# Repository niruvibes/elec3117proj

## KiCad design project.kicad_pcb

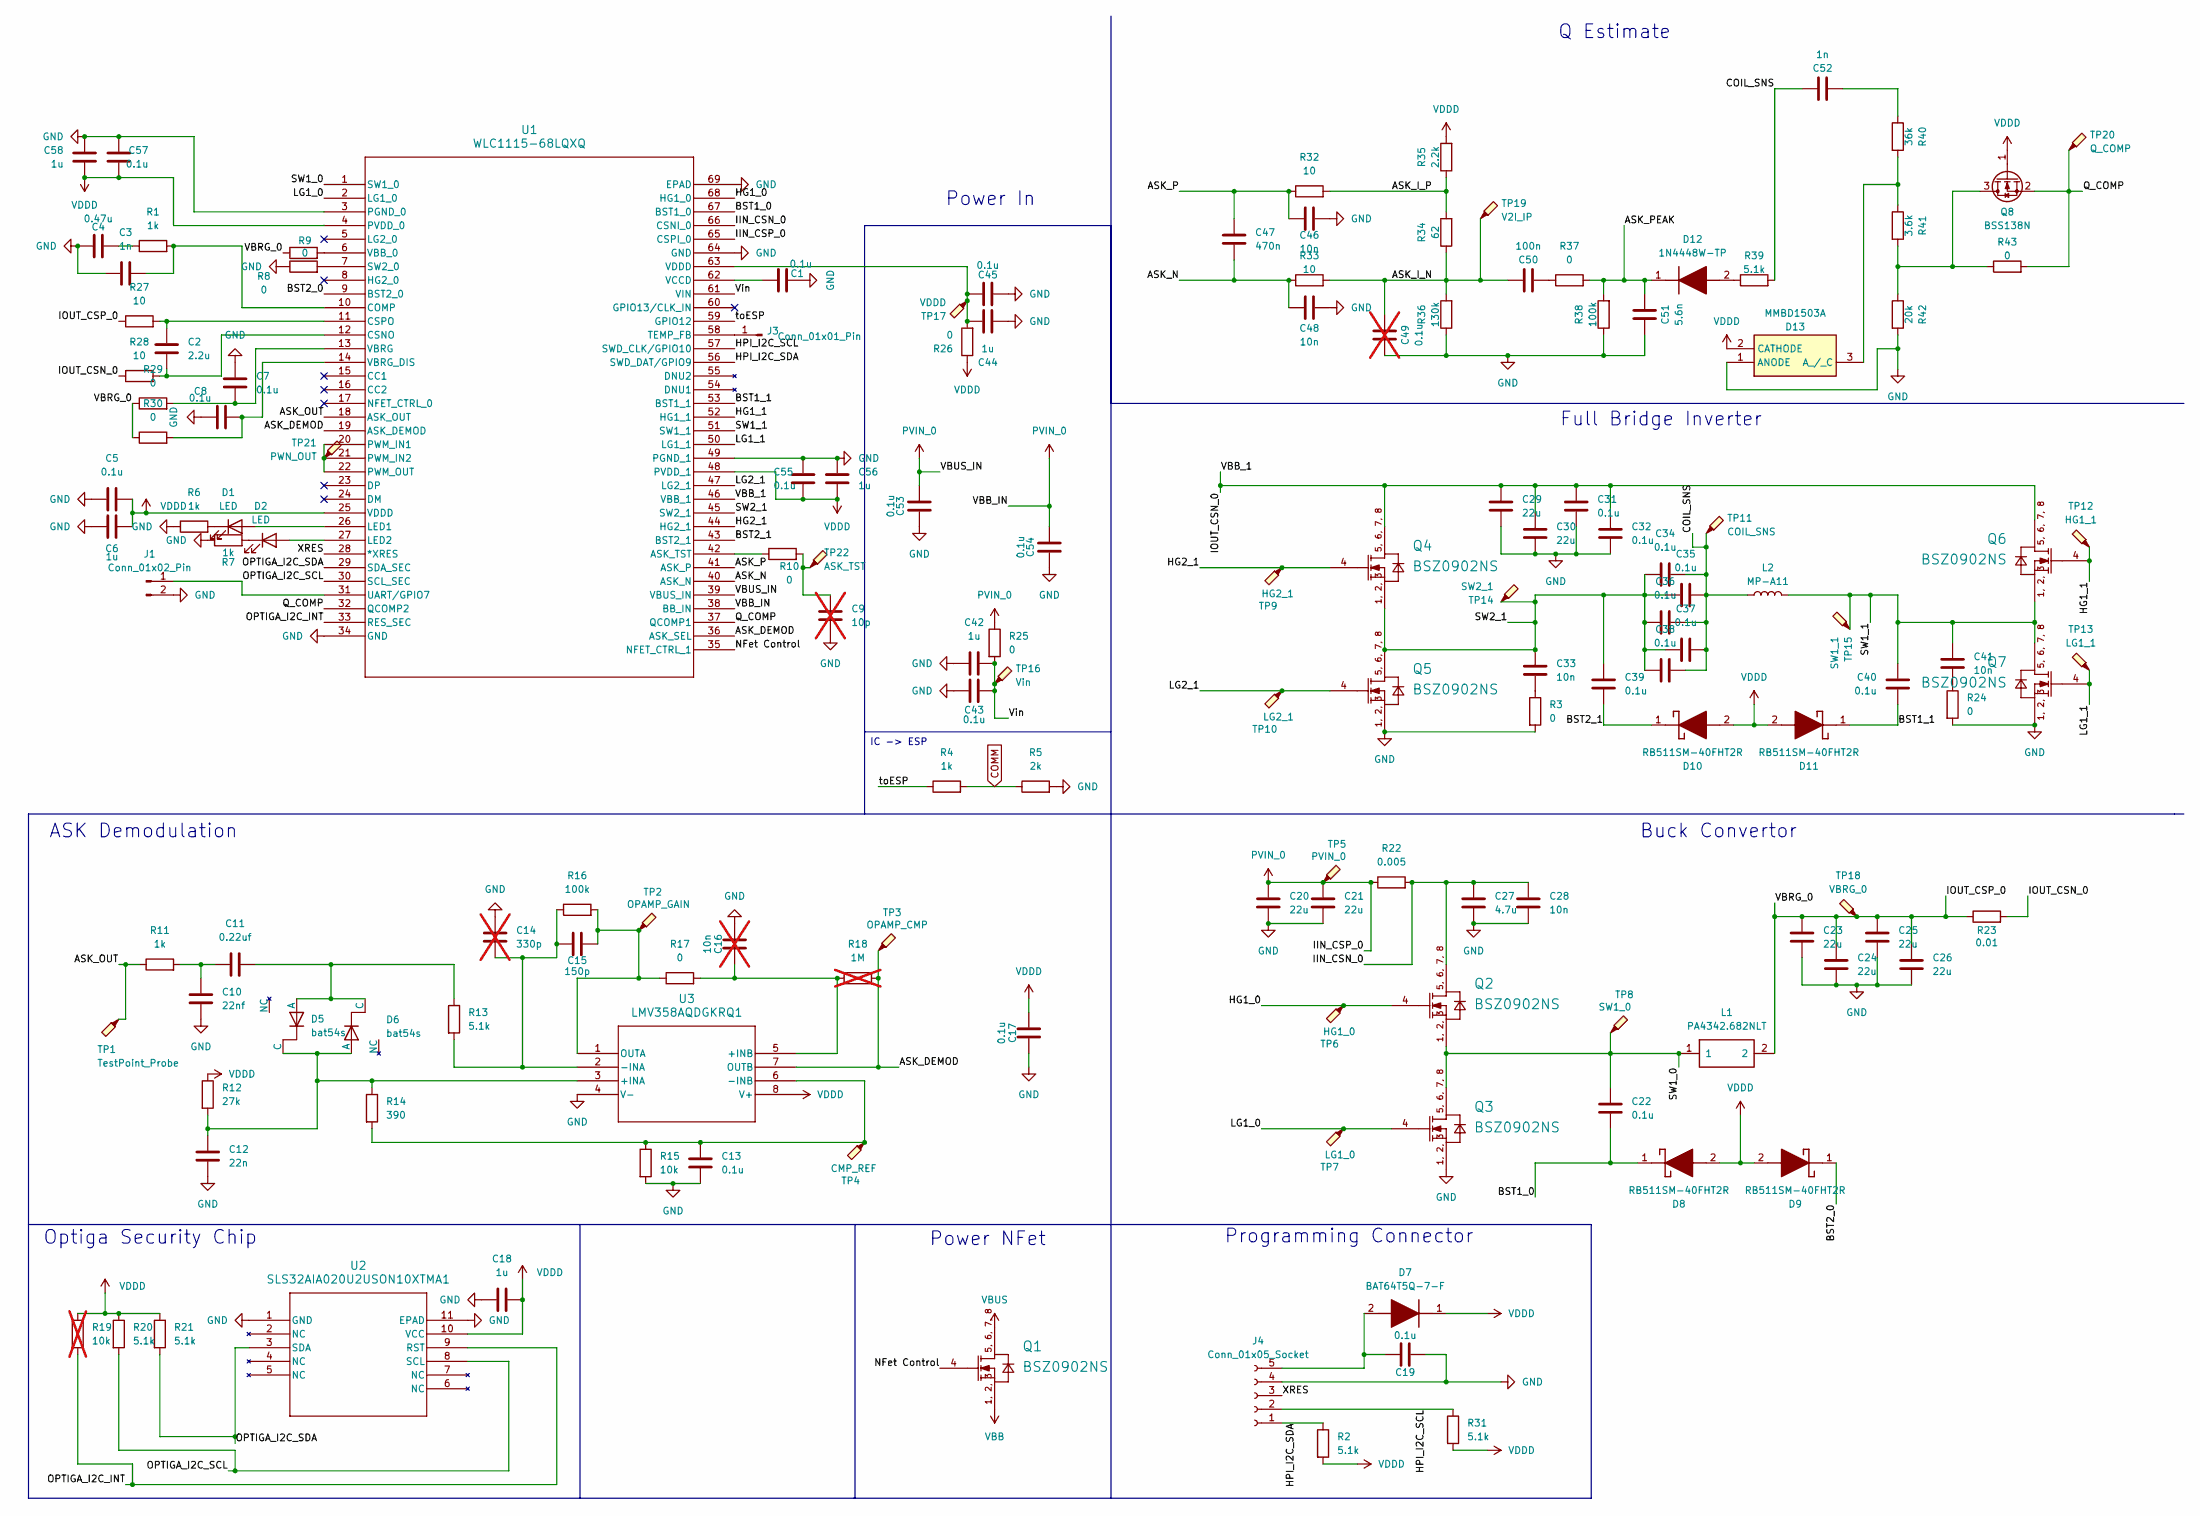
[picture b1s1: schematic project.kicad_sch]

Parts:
C1, C5, C7, C8, C13, C17, C19, C22, C31, C32, C34, C35, C36, C37, C38, C39, C40, C43, C45, C53, C54, C55, C57: 0.1u; C_0603_1608Metric_Pad1.08x0.95mm_HandSolder
C2: 2.2u; C_0603_1608Metric_Pad1.08x0.95mm_HandSolder
C3, C52: 1n; C_0603_1608Metric_Pad1.08x0.95mm_HandSolder
C4: 0.47u; C_0603_1608Metric_Pad1.08x0.95mm_HandSolder
C6, C18, C42, C44, C56, C58: 1u; C_0603_1608Metric_Pad1.08x0.95mm_HandSolder
C9: 10p; C_0603_1608Metric_Pad1.08x0.95mm_HandSolder; not fitted
C10: 22nf; C_0603_1608Metric_Pad1.08x0.95mm_HandSolder
C11: 0.22uf; C_0603_1608Metric_Pad1.08x0.95mm_HandSolder
C12: 22n; C_0603_1608Metric_Pad1.08x0.95mm_HandSolder
C14: 330p; C_0603_1608Metric_Pad1.08x0.95mm_HandSolder; not fitted
C15: 150p; C_0603_1608Metric_Pad1.08x0.95mm_HandSolder
C16: 10n; C_0603_1608Metric_Pad1.08x0.95mm_HandSolder; not fitted
C20, C21, C23, C24, C25, C26, C29, C30: 22u; C_0603_1608Metric_Pad1.08x0.95mm_HandSolder
C27: 4.7u; C_0603_1608Metric_Pad1.08x0.95mm_HandSolder
C28, C33, C41, C46, C48: 10n; C_0603_1608Metric_Pad1.08x0.95mm_HandSolder
C47: 470n; C_0603_1608Metric_Pad1.08x0.95mm_HandSolder
C49: 0.1u; C_0603_1608Metric_Pad1.08x0.95mm_HandSolder; not fitted
C50: 100n; C_0603_1608Metric_Pad1.08x0.95mm_HandSolder
C51: 5.6n; C_0603_1608Metric_Pad1.08x0.95mm_HandSolder
D1, D2: LED; LED_0201_0603Metric_Pad0.64x0.40mm_HandSolder
D5, D6: bat54s; P200_SOT-23
D7: BAT64T5Q-7-F; SODFL1608X65N; Manufacturer_Part_Number BAT64T5Q-7-F; Mouser Part Number 621-BAT64T5Q-7-F
D8, D9, D10, D11: RB511SM-40FHT2R; RB511SM40FHT2R; Manufacturer_Part_Number RB511SM-40FHT2R; Mouser Part Number 755-RB511SM-40FHT2R
D12: 1N4448W-TP; SOD3716X135N; Manufacturer_Part_Number 1N4448W-TP; Mouser Part Number 833-1N4448W-TP
D13: MMBD1503A; SOT95P240X120-3N; Manufacturer_Part_Number MMBD1503A; Mouser Part Number 512-MMBD1503A
J1: Conn_01x02_Pin; PinHeader_1x02_P2.54mm_Vertical
J3: Conn_01x01_Pin; PinHeader_1x01_P2.54mm_Vertical
J4: Conn_01x05_Socket; PinHeader_1x05_P2.54mm_Vertical
L1: PA4342.682NLT; Yageo_Pulse_PA4342_10.3x11.5mm; MPN PA4342.682NLT
L2: MP-A11; TerminalBlock_Phoenix_MKDS-1,5-2-5.08_1x02_P5.08mm_Horizont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
Q1, Q2, Q3, Q4, Q5, Q6, Q7: BSZ0902NS; IFX-PG-TSDSON-8-26-V
Q8: BSS138N; SOT-23
R1, R4, R6, R7, R11: 1k; R_0603_1608Metric_Pad0.98x0.95mm_HandSolder
R2, R13, R20, R21, R31, R39: 5.1k; R_0603_1608Metric_Pad0.98x0.95mm_HandSolder
R3, R8, R9, R10, R17, R24, R25, R26, R29, R30, R37, R43: 0; R_0603_1608Metric_Pad0.98x0.95mm_HandSolder
R5: 2k; R_0603_1608Metric_Pad0.98x0.95mm_HandSolder
R12: 27k; R_0603_1608Metric_Pad0.98x0.95mm_HandSolder
R14: 390; R_0603_1608Metric_Pad0.98x0.95mm_HandSolder
R15: 10k; R_0603_1608Metric_Pad0.98x0.95mm_HandSolder
R16, R38: 100k; R_0603_1608Metric_Pad0.98x0.95mm_HandSolder
R18: 1M; R_0603_1608Metric_Pad0.98x0.95mm_HandSolder; not fitted
R19: 10k; R_0603_1608Metric_Pad0.98x0.95mm_HandSolder; not fitted
R22: 0.005; R_0603_1608Metric_Pad0.98x0.95mm_HandSolder
R23: 0.01; R_0603_1608Metric_Pad0.98x0.95mm_HandSolder
R27, R28, R32, R33: 10; R_0603_1608Metric_Pad0.98x0.95mm_HandSolder
R34: 62; R_0603_1608Metric_Pad0.98x0.95mm_HandSolder
R35: 2.2k; R_0603_1608Metric_Pad0.98x0.95mm_HandSolder
R36: 130k; R_0603_1608Metric_Pad0.98x0.95mm_HandSolder
R40: 36k; R_0603_1608Metric_Pad0.98x0.95mm_HandSolder
R41: 3.6k; R_0603_1608Metric_Pad0.98x0.95mm_HandSolder
R42: 20k; R_0603_1608Metric_Pad0.98x0.95mm_HandSolder
TP1: TestPoint_Probe; TestPoint_Pad_D2.0mm
TP2: OPAMP_GAIN; TestPoint_Pad_D2.0mm
TP3: OPAMP_CMP; TestPoint_Pad_D2.0mm
TP4: CMP_REF; TestPoint_Pad_D2.0mm
TP5: PVIN_0; TestPoint_Pad_D2.0mm
TP6: HG1_0; TestPoint_Pad_D2.0mm
TP7: LG1_0; TestPoint_Pad_D2.0mm
TP8: SW1_0; TestPoint_Pad_D2.0mm
TP9: HG2_1; TestPoint_Pad_D2.0mm
TP10: LG2_1; TestPoint_Pad_D2.0mm
TP11: COIL_SNS; TestPoint_Pad_D2.0mm
TP12: HG1_1; TestPoint_Pad_D2.0mm
TP13: LG1_1; TestPoint_Pad_D2.0mm
TP14: SW2_1; TestPoint_Pad_D2.0mm
TP15: SW1_1; TestPoint_Pad_D2.0mm
TP16: Vin; TestPoint_Pad_D2.0mm
TP17: VDDD; TestPoint_Pad_D2.0mm
TP18: VBRG_0; TestPoint_Pad_D2.0mm
TP19: V2I_IP; TestPoint_Pad_D2.0mm
TP20: Q_COMP; TestPoint_Pad_D2.0mm
TP21: PWN_OUT; TestPoint_Pad_D2.0mm
TP22: ASK_TST; TestPoint_Pad_D2.0mm
U1: WLC1115-68LQXQ; PG-VQFN-68
U2: SLS32AIA020U2USON10XTMA1; PG-USON-10-2
U3: LMV358AQDGKRQ1; DGK8_TEX

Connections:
/ASK_DEMOD: R18.2, TP3.1 (1_1), U1.19 (ASK_DEMOD), U1.36 (ASK_SEL), U3.7 (OUTB)
/ASK_I_N: C49.2, C50.2, R33.2, R34.1, R36.2, TP19.1 (1_1)
/ASK_I_P: R32.2, R34.2, R35.1
/ASK_N: C47.1, C48.1, R33.1, U1.40 (ASK_N)
/ASK_OUT: R11.1, TP1.1 (1_1), U1.18 (ASK_OUT)
/ASK_P: C46.1, C47.2, R32.1, U1.41 (ASK_P)
/ASK_PEAK: C51.2, D12.1 (K), R37.2, R38.2
/BST1_0: C22.2, D8.1 (K), U1.67 (BST1_0)
/BST1_1: C40.1, D11.1 (K), U1.53 (BST1_1); also elsewhere on the board
/BST2_0: D9.1 (K), U1.9 (BST2_0)
/BST2_1: C39.1, D10.1 (K), U1.43 (BST2_1)
/COIL_SNS: C34.2, C35.2, C36.2, C37.2, C38.2, C52.2, L2.1, R39.2, TP11.1 (1_1)
/HG1_0: Q2.4 (GATE), TP6.1 (1_1), U1.68 (HG1_0)
/HG1_1: Q6.4 (GATE), TP12.1 (1_1), U1.52 (HG1_1)
/HG2_1: Q4.4 (GATE), TP9.1 (1_1), U1.44 (HG2_1)
/HPI_I2C_SCL: J4.2, R31.1, U1.57 (SWD_CLK/GPIO10)
/HPI_I2C_SDA: J4.1, R2.1, U1.56 (SWD_DAT/GPIO9)
/IIN_CSN_0: C27.1, C28.1, Q2.5 (DRAIN), Q2.6 (DRAIN), Q2.7 (DRAIN), Q2.8 (DRAIN), R22.2, U1.66 (CSNI_0)
/IOUT_CSN_0: C29.1, C30.1, C31.1, C32.1, Q4.5 (DRAIN), Q4.6 (DRAIN), Q4.7 (DRAIN), Q4.8 (DRAIN), Q6.5 (DRAIN), Q6.6 (DRAIN), Q6.7 (DRAIN), Q6.8 (DRAIN), R23.2, R28.1, U1.46 (VBB_1)
/IOUT_CSP_0: C23.1, C24.1, C25.1, C26.1, L1.2, R9.1, R23.1, R27.1, R29.1, R30.1, TP18.1 (1_1)
/LG1_0: Q3.4 (GATE), TP7.1 (1_1), U1.2 (LG1_0)
/LG1_1: Q7.4 (GATE), TP13.1 (1_1), U1.50 (LG1_1)
/LG2_1: Q5.4 (GATE), TP10.1 (1_1), U1.47 (LG2_1)
/NFet Control: Q1.4 (GATE), U1.35 (NFET_CTRL_1)
/OPTIGA_I2C_INT: R19.2, U1.33 (RES_SEC), U2.9 (RST)
/OPTIGA_I2C_SCL: R20.2, U1.30 (SCL_SEC), U2.8 (SCL)
/OPTIGA_I2C_SDA: R21.2, U1.29 (SDA_SEC), U2.3 (SDA)
/Q_COMP: Q8.2 (S), R43.2, TP20.1 (1_1), U1.32 (QCOMP2), U1.37 (QCOMP1)
/SW1_0: C22.1, L1.1, Q2.1 (SOURCE), Q2.2 (SOURCE), Q2.3 (SOURCE), Q3.5 (DRAIN), Q3.6 (DRAIN), Q3.7 (DRAIN), Q3.8 (DRAIN), TP8.1 (1_1), U1.1 (SW1_0)
/SW1_1: C40.2, C41.1, L2.2, Q6.1 (SOURCE), Q6.2 (SOURCE), Q6.3 (SOURCE), Q7.5 (DRAIN), Q7.6 (DRAIN), Q7.7 (DRAIN), Q7.8 (DRAIN), TP15.1 (1_1), U1.51 (SW1_1); also elsewhere on the board
/SW2_1: C33.1, C34.1, C35.1, C36.1, C37.1, C38.1, C39.2, Q4.1 (SOURCE), Q4.2 (SOURCE), Q4.3 (SOURCE), Q5.5 (DRAIN), Q5.6 (DRAIN), Q5.7 (DRAIN), Q5.8 (DRAIN), TP14.1 (1_1), U1.45 (SW2_1)
/Vin: C42.2, C43.2, R25.2, TP16.1 (1_1), U1.61 (VIN)
/XRES: J4.3, U1.28 (*XRES)
/toESP: R4.1, U1.59 (GPIO12)
COMM: R4.2, R5.1
GND: C1.2, C3.1, C4.1, C5.1, C6.1, C7.1, C8.1, C9.2, C10.2, C12.2, C13.2, C14.1, C16.1, C17.2, C18.1, C19.2, C20.2, C21.2, C23.2, C24.2, C25.2, C26.2, C27.2, C28.2, C29.2, C30.2, C31.2, C32.2, C42.1, C43.1, C44.1, C45.1, C46.2, C48.2, C49.1, C51.1, C53.2, C54.2, C55.1, C56.1, C57.1, C58.1, D13.1 (ANODE), J1.2, J4.4, Q3.1 (SOURCE), Q3.2 (SOURCE), Q3.3 (SOURCE), Q5.1 (SOURCE), Q5.2 (SOURCE), Q5.3 (SOURCE), Q7.1 (SOURCE), Q7.2 (SOURCE), Q7.3 (SOURCE), R3.2, R5.2, R6.1, R7.1, R8.1, R15.2, R24.2, R36.1, R38.1, R42.2, U1.3 (PGND_0), U1.34 (GND), U1.49 (PGND_1), U1.64 (GND), U1.69 (EPAD), U2.1 (GND), U2.11 (EPAD), U3.4 (V-)
unnamed: C4.2, R1.1
unnamed: C9.1, R10.2, TP22.1 (1_1)
unnamed: C10.1, C11.1, R11.2
unnamed: C33.2, R3.1
unnamed: C41.2, R24.1
unnamed: C44.2, C45.2, R26.2, TP17.1 (1_1), U1.63 (VDDD)
unnamed: C50.1, R37.1
unnamed: C52.1, R40.1
unnamed: D1.2 (A), U1.26 (LED1)
unnamed: D1.1 (K), R6.2
unnamed: D2.2 (A), U1.27 (LED2)
unnamed: D2.1 (K), R7.2
unnamed: C11.2, D5.1 (A), D6.2 (C), R13.1
unnamed: C12.1, D5.2 (C), D6.1 (A), R12.2, R14.1, U3.3 (+INA)
unnamed: C19.1, D7.2 (A), J4.5
unnamed: D12.2 (A), R39.1
unnamed: D13.3 (A_/_C), R40.2, R41.1
unnamed: J1.1, U1.31 (UART/GPIO7)
unnamed: J3.1 (Pin_1_1), U1.58 (TEMP_FB)
unnamed: Q8.3 (D), R41.2, R42.1, R43.1
unnamed: R10.1, U1.42 (ASK_TST)
unnamed: C3.2, R1.2, U1.10 (COMP)
unnamed: C2.2, R28.2, U1.12 (CSNO)
unnamed: C2.1, R27.2, U1.11 (CSPO)
unnamed: TP21.1 (1_1), U1.20 (PWM_IN1), U1.21 (PWM_IN2), U1.22 (PWM_OUT)
unnamed: R8.2, U1.7 (SW2_0)
unnamed: R9.2, U1.6 (VBB_0)
unnamed: C7.2, R29.2, U1.13 (VBRG)
unnamed: C8.2, R30.2, U1.14 (VBRG_DIS)
unnamed: C1.1, U1.62 (VCCD)
unnamed: C16.2, R17.2, R18.1, U3.5 (+INB)
unnamed: C14.2, C15.1, R13.2, R16.1, U3.2 (-INA)
unnamed: C13.1, R14.2, R15.1, TP4.1 (1_1), U3.6 (-INB)
unnamed: C15.2, R16.2, R17.1, TP2.1 (1_1), U3.1 (OUTA)
PVIN_0: C20.1, C21.1, C53.1, C54.1, R22.1, R25.1, TP5.1 (1_1), U1.38 (BB_IN), U1.39 (VBUS_IN), U1.65 (CSPI_0)
VBB: Q1.1 (SOURCE), Q1.2 (SOURCE), Q1.3 (SOURCE)
VBUS: Q1.5 (DRAIN), Q1.6 (DRAIN), Q1.7 (DRAIN), Q1.8 (DRAIN)
VDDD: C5.2, C6.2, C17.1, C18.2, C55.2, C56.2, C57.2, C58.2, D7.1 (K), D8.2 (A), D9.2 (A), D10.2 (A), D11.2 (A), D13.2 (CATHODE), Q8.1 (G), R2.2, R12.1, R19.1, R20.1, R21.1, R26.1, R31.2, R35.2, U1.4 (PVDD_0), U1.25 (VDDD), U1.48 (PVDD_1), U2.10 (VCC), U3.8 (V+)

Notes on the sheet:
Optiga Security Chip
Full Bridge Inverter
ASK Demodulation
IC -> ESP
Programming Connector
Q Estimate
Buck Convertor
Power NFet
Power In

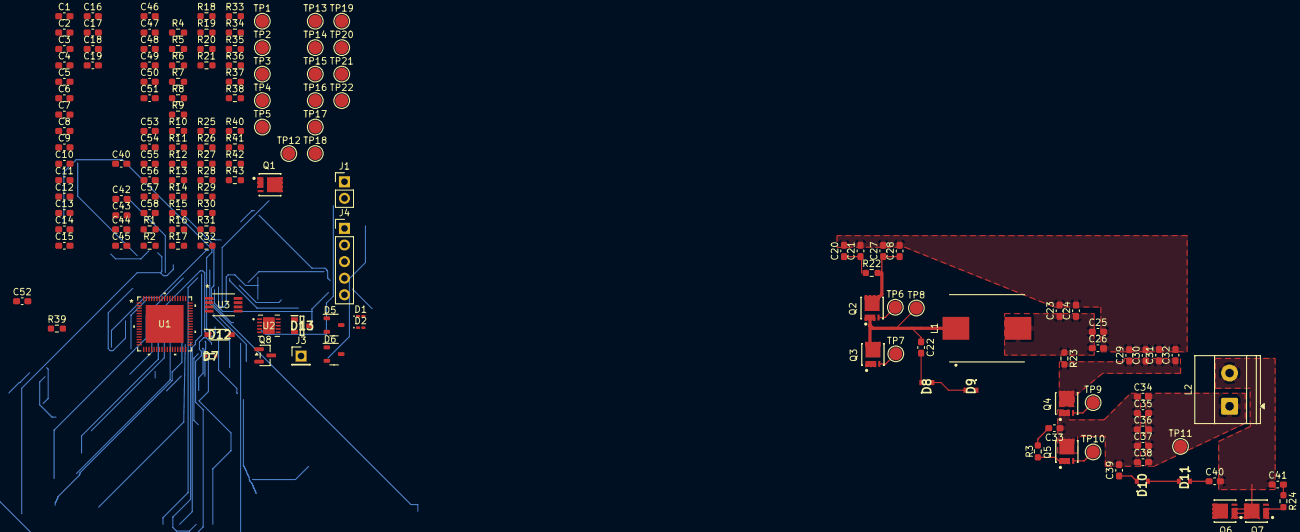
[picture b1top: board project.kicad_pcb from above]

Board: 2 copper layers, 151 parts (0 on the bottom side), 74 nets.

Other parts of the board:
C40#2: 0.1u; C_0603_1608Metric_Pad1.08x0.95mm_HandSolder

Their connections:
/BST1_1: C40#2.1; also elsewhere on the board
/SW1_1: C40#2.2; also elsewhere on the board

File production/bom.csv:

Designator,Footprint,Quantity,Value,LCSC Part #
"C1, C13, C17, C19, C31, C32, C40, C43, C45, C49, C5, C7",0603,12,0.1u,
C10,0603,1,22nf,
C11,0603,1,0.22uf,
C12,0603,1,22n,
C14,0603,1,330p,
C15,0603,1,150p,
"C16, C28, C33, C41, C46, C48",0603,6,10n,
"C18, C42, C6",0603,3,1u,
C2,0603,1,2.2u,
"C20, C21, C23, C24, C25, C26",1206,6,22u,
"C22, C39, C53, C54, C55, C57, C8",0402,7,0.1u,
C27,0805,1,4.7u,
C29,0805,1,22u,
"C3, C52",0603,2,1n,
C30,0603,1,22u,
"C34, C35, C36, C37, C38",1206,5,0.1u,
C4,0603,1,0.47u,
C44,0805,1,1u,
C47,0402,1,470n,
C50,0603,1,100n,
C51,0603,1,5.6n,
"C56, C58",0402,2,1u,
C9,0402,1,10p,
"D1, D2",0201,2,LED,
"D10, D11, D8, D9",D_SOD-523,4,RB511SM-40FHT2R,
D12,SOD3716X135N,1,1N4448W-TP,
D13,SOT95P240X120-3N,1,MMBD1503A,
D7,SODFL1608X65N,1,BAT64T5Q-7-F,
IC1,SOT65P210X100-3N,1,BAT5404WH6327XTSA1,
"J1, J2",PinHeader_1x02_P2.54mm_Horizontal,2,Conn_01x02_Pin,
J3,PinHeader_1x01_P2.54mm_Horizontal,1,Conn_01x01_Pin,
J4,PinHeader_1x05_P2.54mm_Horizontal,1,Conn_01x05_Socket,
J5,SolderWire-0.5sqmm_1x02_P4.8mm_D0.9mm_OD2.3mm,1,Conn_01x02,
L1,Yageo_Pulse_PA4342_10.3x11.5mm,1,PA4342.682NLT,PA4342.682NLT
L2,"TerminalBlock_Phoenix_MKDS-1,5-2-5.08_1x02_P5.08mm_Horizontal",1,MP-A11,
"Q2, Q3, Q4, Q5, Q6, Q7",IFX-PG-TSDSON-8-26-V,6,BSZ0902NS,
Q8,SOT-23,1,BSS138N,
"R1, R11, R6, R7",0603,4,1k,
"R10, R30, R43, R8, R9",0402,5,0,
R12,0603,1,27k,
"R13, R2, R20, R21, R31, R39",0603,6,5.1k,
R14,0603,1,390,
"R15, R19",0603,2,10k,
"R16, R38",0603,2,100k,
"R17, R24, R25, R29, R3, R37",0603,6,0,
R18,0603,1,1M,
R22,1206,1,0.005,
R23,1206,1,0.01,
"R27, R28",0402,2,10,
"R32, R33",0603,2,10,
R34,0603,1,62,
R35,0603,1,2.2k,
R36,0603,1,130k,
R40,0603,1,36k,
R41,0603,1,3.6k,
R42,0603,1,20k,
TP1,TestPoint_Pad_D1.5mm,1,ASK_OUT,
TP10,TestPoint_Pad_D1.0mm,1,LG2_1,
TP11,TestPoint_Pad_D2.0mm,1,COIL_SNS,
TP12,TestPoint_Pad_D2.0mm,1,HG1_1,
TP13,TestPoint_Pad_D2.0mm,1,LG1_1,
TP14,TestPoint_Pad_D2.0mm,1,SW2_1,
TP15,TestPoint_Pad_D2.0mm,1,SW1_1,
TP16,TestPoint_Pad_D1.5mm,1,Vin,
TP17,TestPoint_Pad_D1.5mm,1,VDDD,
TP18,TestPoint_Pad_D2.0mm,1,VBRG_0,
TP19,TestPoint_Pad_D2.0mm,1,V2I_IP,
TP2,TestPoint_Pad_D2.0mm,1,OPAMP_GAIN,
TP20,TestPoint_Pad_D2.0mm,1,Q_COMP,
TP21,TestPoint_Pad_D1.0mm,1,PWN_OUT,
TP22,TestPoint_Pad_D1.0mm,1,ASK_TST,
TP23,TestPoint_Pad_D1.0mm,1,VCCD,
TP3,TestPoint_Pad_D2.0mm,1,OPAMP_CMP,
TP4,TestPoint_Pad_D2.0mm,1,CMP_REF,
TP5,TestPoint_Pad_D2.0mm,1,PVIN_0,
TP6,TestPoint_Pad_D1.0mm,1,HG1_0,
TP7,TestPoint_Pad_D1.0mm,1,LG1_0,
TP8,TestPoint_Pad_D1.5mm,1,SW1_0,
TP9,TestPoint_Pad_D1.0mm,1,HG2_1,
U1,PG-VQFN-68,1,WLC1115-68LQXQ,
U2,PG-USON-10-2,1,SLS32AIA020U2USON10XTMA1,
U3,DGK8_TEX,1,LMV358AQDGKRQ1,
